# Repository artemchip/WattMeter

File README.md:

# Умный электросчетчик
Учет расхода энергии в сетях 220В с помощью трансформатора тока.  
Устройство:  

UI:  

Скоро возможно будет функция постройки графиков.

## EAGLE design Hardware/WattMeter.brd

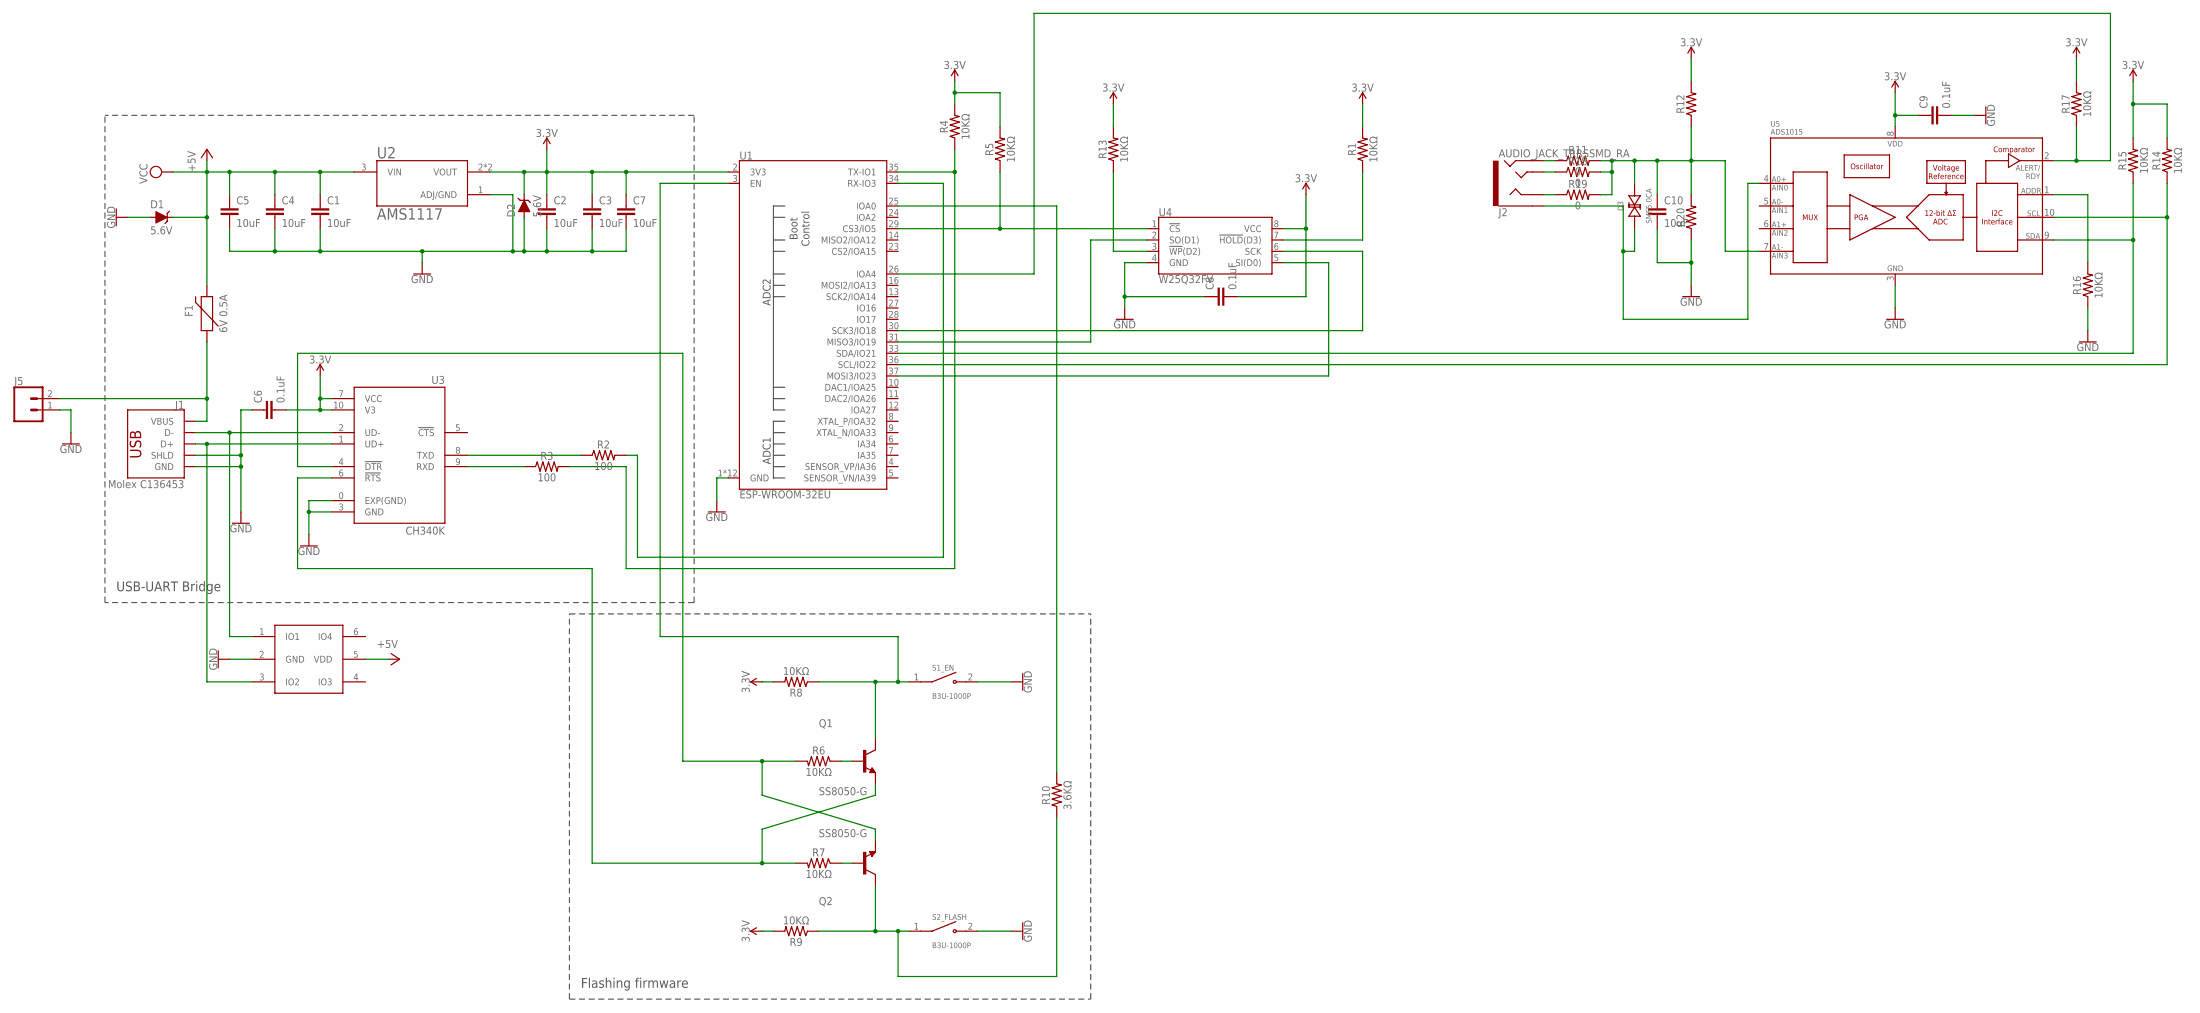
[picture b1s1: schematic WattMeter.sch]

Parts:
C1, C2, C3, C4, C5, C7, C10: 10uF; 0603
C6, C8, C9: 0.1uF; 0402
D1, D2: 5.6V; SOD-323
D3: SMF5.0CA; SOD-123FL
F1: 6V 0.5A; 0805
J1: Molex C136453; USB-A-SMT-MALE
J2: AUDIO_JACK_TRRSSMD_RA; AUDIO_JACK_3.5MM_TRRS_SMD_RA
J5: CONN_023.5MM; SCREWTERMINAL-3.5MM-2
Q1, Q2: SS8050-G; TRANS_SS8050-G
R1, R4, R5, R6, R7, R8, R9, R13, R14, R15, R16, R17: 10KΩ; 0402-TIGHT
R2, R3: 100; 0402-TIGHT
R10: 3.6KΩ; 0402-TIGHT
R11, R18, R19: 0; 0402
R12, R20: 10KΩ; 0402
S1_EN, S2_FLASH: B3U-1000P; SW_B3U-1000P
U1: ESP-WROOM-32EU
U2: AMS1117; SOT229P700X180-4N
U3: CH340K; SOP100P600X160-11N
U4: W25Q32FV; SOIC-8
U5: ADS1015; MSOP10
U6: AZC099-04S; SOT95P275X110-6N

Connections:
3.3V: C2.1, C3.1, C6.2, C7.1, C8.2, C9.1, D2.C, R1.2, R4.2, R5.2, R8.2, R9.2, R12.2, R13.2, R14.2, R15.2, R17.2, U1.2 (3V3), U2.2 (VOUT), U2.4 (VOUT), U3.7 (VCC), U3.10 (V3), U4.8 (VCC), U5.8 (VDD)
+5V: C1.1, C4.1, C5.1, D1.C, F1.2, U2.3 (VIN), U6.5 (VDD)
GND: C1.2, C2.2, C3.2, C4.2, C5.2, C6.1, C7.2, C8.1, C9.2, C10.2, D1.A, D2.A, J1.GND1 (GND), J1.SHLD1 (SHLD), J1.SHLD2 (SHLD), J5.1, R16.1, R20.1, S1_EN.2, S2_FLASH.2, U1.1 (GND), U1.15 (GND), U1.38 (GND), U1.GND, U1.GNDT1 (GND), U1.GNDT2 (GND), U1.GNDT3 (GND), U1.GNDT4 (GND), U1.GNDT5 (GND), U1.GNDT6 (GND), U1.GNDT7 (GND), U1.GNDT8 (GND), U2.1 (ADJ/GND), U3.0 (EXP(GND)), U3.3 (GND), U4.4 (GND), U5.3 (VSS), U6.2 (GND)
unnamed: J1.D-1 (D-), U3.2 (UD-), U6.1 (IO1)
unnamed: U1.31 (MISO3/IO19), U4.2 (SO(D1))
unnamed: J1.D+1 (D+), U3.1 (UD+), U6.3 (IO2)
unnamed: Q2.1 (B), R7.1
unnamed: R2.1, U3.8 (TXD)
unnamed: Q2.2 (E), R6.2, U3.4 (!DTR)
unnamed: Q1.2 (E), R7.2, U3.6 (!RTS)
unnamed: R3.1, U3.9 (RXD)
unnamed: U1.37 (MOSI3/IO23), U4.5 (SI(D0))
unnamed: U1.30 (SCK3/IO18), U4.6 (SCK)
unnamed: R1.1, U4.7 (!HOLD!(D3))
unnamed: Q2.3 (C), R9.1, R10.1, S2_FLASH.1
unnamed: Q1.1 (B), R6.1
unnamed: R3.2, R4.1, U1.35 (TX-IO1)
unnamed: R2.2, U1.34 (RX-IO3)
unnamed: R5.1, U1.29 (CS3/IO5), U4.1 (!CS!)
unnamed: R13.1, U4.3 (!WP!(D2))
unnamed: Q1.3 (C), R8.1, S1_EN.1, U1.3 (EN)
unnamed: R10.2, U1.25 (IOA0)
unnamed: R15.1, U1.33 (SDA/IO21), U5.9 (SDA)
unnamed: R14.1, U1.36 (SCL/IO22), U5.10 (SCL)
unnamed: D3.P$1 (1), J2.EARTH, U5.4 (AIN0)
unnamed: R16.2, U5.1 (ADDR)
unnamed: R17.1, U1.26 (IOA4), U5.2 (ALERT/RDY)
unnamed: C10.1, D3.P$2 (2), R11.2, R12.1, R18.2, R19.2, R20.2, U5.7 (AIN3)
unnamed: J2.RING2, R11.1
unnamed: F1.1, J1.VBUS1 (VBUS), J5.2
unnamed: J2.TIP, R18.1
unnamed: J2.RING1, R19.1

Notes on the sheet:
Flashing firmware
USB-UART Bridge

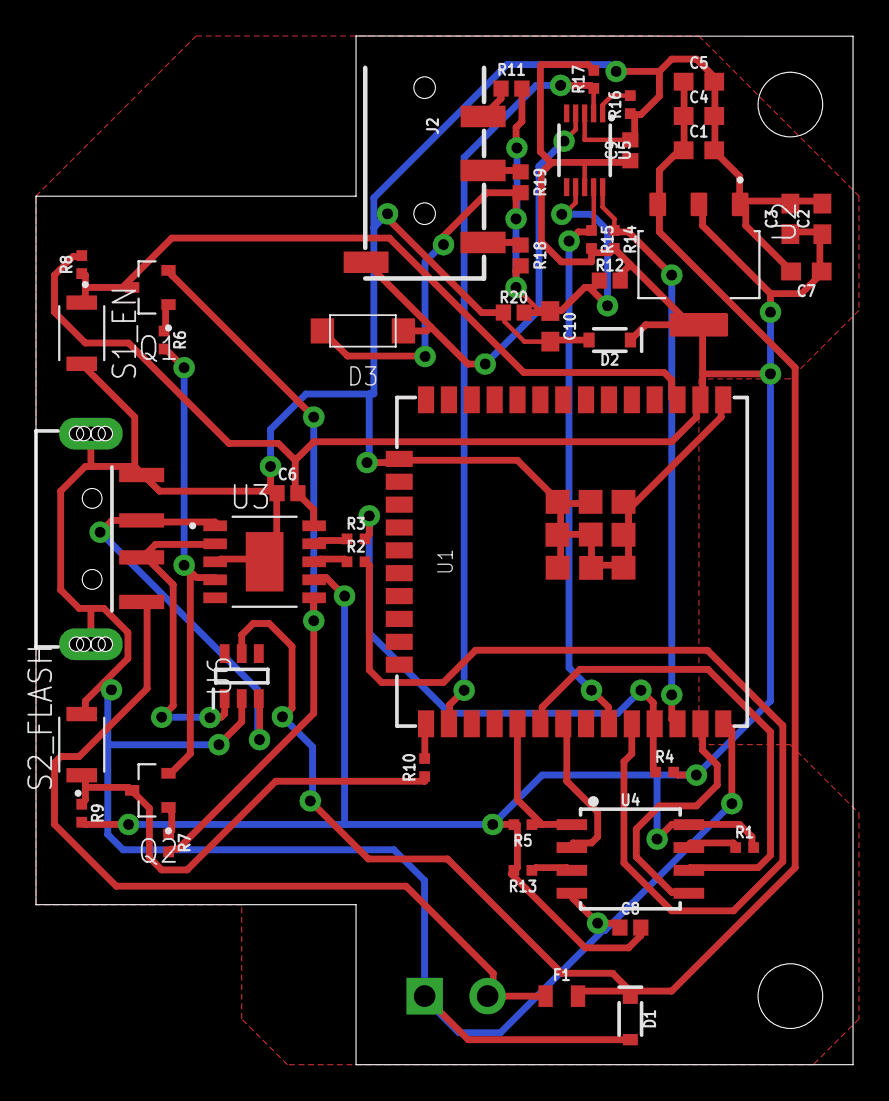
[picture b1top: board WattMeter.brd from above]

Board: 2 copper layers, 45.4 x 57.1 mm, 47 parts (1 on the bottom side), 32 nets.

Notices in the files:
parts and their libraries:
SparkFun-Capacitors: Licensing: Creative Commons ShareAlike 4.0 International - https://creativecommons.org/licenses/by-sa/4.0
